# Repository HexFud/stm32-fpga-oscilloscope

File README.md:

# stm32-fpga-oscilloscope
I created a 1-Channel 20MHz 100MS/s Mixed-Signal Digital Storage Oscilloscope on a custom 4-layer PCB. Powered by STM32H7, Lattice iCE40 FPGA, and USB-C from scratch!

## Project overview

The project is made of three parts that were designed together, because each one constrains the others: the PCB decides what the firmware can do, and the heat generated on the PCB decides how the enclosure is built.

| Part | What it covers | Tools |
| :--- | :--- | :--- |
| **PCB** | Schematic and 4-layer layout (see [Schematic and Routing](#schematic-and-routing) and [How this was made](#how-this-was-made)) | KiCad |
| **Firmware** | Acquisition, trigger, signal processing, waveform rendering and UI (see [Firmware](#firmware) and [Firmware architecture](#firmware-architecture)) | STM32CubeIDE, STM32 HAL |
| **CAD** | 3D-printable enclosure (see [Enclosure (CAD)](#enclosure-cad)) | **TODO:** CAD software |

## Schematic and Routing

## How this was made

I have designed the PCB starting from an STM32H7 microcontroller because of its support for external SRAM and it can directly control the main 7 Inch display with high speed transmission data. The entire board runs using a single 5V usb-C connection and then internally this becomes 3.3V, 1.2V and ±5V. The board includes connections for:
- A standard BNC input for oscilloscope probes (1MΩ impedance)
- 2 Rotary encoders and 6 tactile buttons for UI navigation
- A 40-pin FPC socket for an RGB LCD display with a dedicated capacitive touch connector.

## Specifications

| Parameter | Value |
| :--- | :--- |
| Channels | 1 analog |
| Analog bandwidth | 20 MHz |
| Sample rate | 100 MS/s |
| Input | BNC, 1 MΩ, x1 / x10 probes |
| Processing | STM32H7 + Lattice iCE40 FPGA |
| Display | 7" 800x480 RGB LCD, capacitive touch |
| User input | 2 rotary encoders, 6 buttons, touchscreen |
| Power / data | USB-C, 5 V |
| PCB | Custom 4-layer |

## Firmware
The firmware runs on the STM32H7 and is built with STM32CubeIDE and the STM32 HAL. It is responsible for acquisition control, trigger handling, signal processing, rendering the waveform and handling the user interface.

## Display and UI

- Waveform area with a graticule (grid) and a measurement/status bar
- Frame buffer in memory, redrawn on every new acquisition **TODO**
- Controls: one encoder for time base, one for volts/div, buttons for run/stop, single, trigger mode, etc.
- Touchscreen for menus and cursors **TODO**

## Firmware architecture

### Toolchain

| Item | Value |
| :--- | :--- |
| IDE | STM32CubeIDE |
| Drivers | STM32 HAL |
| Language | C |
| Programmer | ST-Link V2 over SWD (J1) |
| Flashing tool | STM32CubeProgrammer |

### Modules

The firmware is organised in layers, from the hardware up to the user interface:

| Layer | Module | Responsibility |
| :--- | :--- | :--- |
| Drivers | Display | Drives the 800x480 RGB panel from a frame buffer |
| Drivers | External memory | Initialises and accesses the external SRAM |
| Drivers | Touch | Reads touch events from the capacitive touch controller |
| Drivers | Input | Reads the 2 encoders and 6 buttons |
| Drivers | FPGA link | Configures the FPGA and transfers captured samples |
| Core | Acquisition | Arms the capture, manages run / stop / single modes and the time base |
| Core | Trigger | Trigger configuration (source, level, slope, mode) |
| Core | Processing | Scaling by volts/div and time/div, measurements |
| UI | Renderer | Draws the graticule, the waveform and the measurement/status bar |
| UI | Controls | Maps encoders, buttons and touch to oscilloscope settings |

### Data flow

1. The ADC samples the input signal and the FPGA captures the samples and evaluates the trigger condition.
2. When a trigger fires, the captured record is transferred to the STM32H7 and stored in memory.
3. The processing stage scales the record to the current volts/div and time/div settings.
4. The renderer draws the graticule and the waveform into the frame buffer, and the display peripheral shows it on screen.
5. Encoder, button and touch events update the settings, and the cycle restarts.

### Testing and debugging

**TODO**

## External connections

1. USB-C Power and Data (P1) this port powers the entire board and it is protected against ESD via a dedicated USBLC6-2SC6 chip
2. Signal Input (J2) It allows you to connect standard x1/x10 oscilloscope probes to measure
3. Programming Port (J1)  Has 3 pins dedicated to flashing and debugging the STM32 microcontroller

| Pin | Function | Where to connect (ST-Link) |
| :---: | :--- | :--- |
| **1** | `SWDIO` | ST-Link SWDIO |
| **2** | `SWCLK` | ST-Link SWCLK |
| **3** | `GND` | ST-Link GND |

## How to flash the firmware

My project uses an STM32H7 chip. To flash the firmware you need an ST-LINK V2 where you need to wire up the correct cable from the usb to the board (J1 connector) and download the free software [STM32CubeProgrammer](https://www.st.com/content/st_com/en/stm32cubeprogrammer.html) and you simply need to upload the firmware.

Steps to reproduce (note that you need to do both):

In STM32CubeIDE:

1. Install STM32CubeIDE
2. Open the project folder inside the IDE
3. Let the IDE resolve the HAL dependencies
4. Go to Project -> Build All to compile the code
5. Wait for the compilation to finish and locate the generated `.bin` or `.elf` file in the `Debug` folder.

In STM32CubeProgrammer:

1. Install the software from the link above
2. Insert the ST-Link V2 USB into the pc
3. Connect the pins explained above (you can power the board via the USB-C port while flashing)
4. In STM32CubeProgrammer ensure that ST-LINK is selected and click connect
5. Go in the erasing & programming tab and select the previously exported `.bin` file
6. Click start programming and if everything went right you'll see Download verified successfully

## Enclosure (CAD)

The enclosure is designed to be 3D printed and to hold the PCB and the 7" display in a single compact unit.

This was designed to:
- Hold the PCB and the 7" display in one unit, with the display window aligned to the active area of the panel
- Expose the BNC input (J2), the USB-C port (P1) and the programming header (J1) without opening the case
- Give access to the 2 rotary encoders and the 6 buttons from the front
- Manage heat: the linear regulators (LDOs) and the FPGA warm up during continuous high-speed sampling, so the enclosure must not trap heat or soften (see the filament recommendation below)

## Filament reccomendation

Because linear regulators (LDOs) and the FPGA generate heat during continuous high-speed sampling, I strongly reccomend to use filaments like PETG, ABS or ASA instead of standard PLA ensuring the plastic won't soften, warp or melt during intensive usage.

## Bill of materials

The full list is in [`bom.csv`](bom.csv). The total is **614.79 USD**. It includes the PCB manufacturing, the 7" display and the parts that are not sourced from LCSC.

## ⚠️⚠️ Safety advice ⚠️⚠️

This project includes experimental software, hardware designs, and assembly documentation are still under development and may contain bugs, errors, or incomplete features. By using, building, or modifying this project, you acknowledge that:

1. You use this project entirely at your own risk
2. You are solely responsible for safe assembly, testing, and operation
3. The autor isn't responsible for any type of damage, injury or loss to people or the machine itself

By proceeding, you accept all risks and agree to these conditions. If you do not acknowledge these risks and conditions, please do not use or build this project.

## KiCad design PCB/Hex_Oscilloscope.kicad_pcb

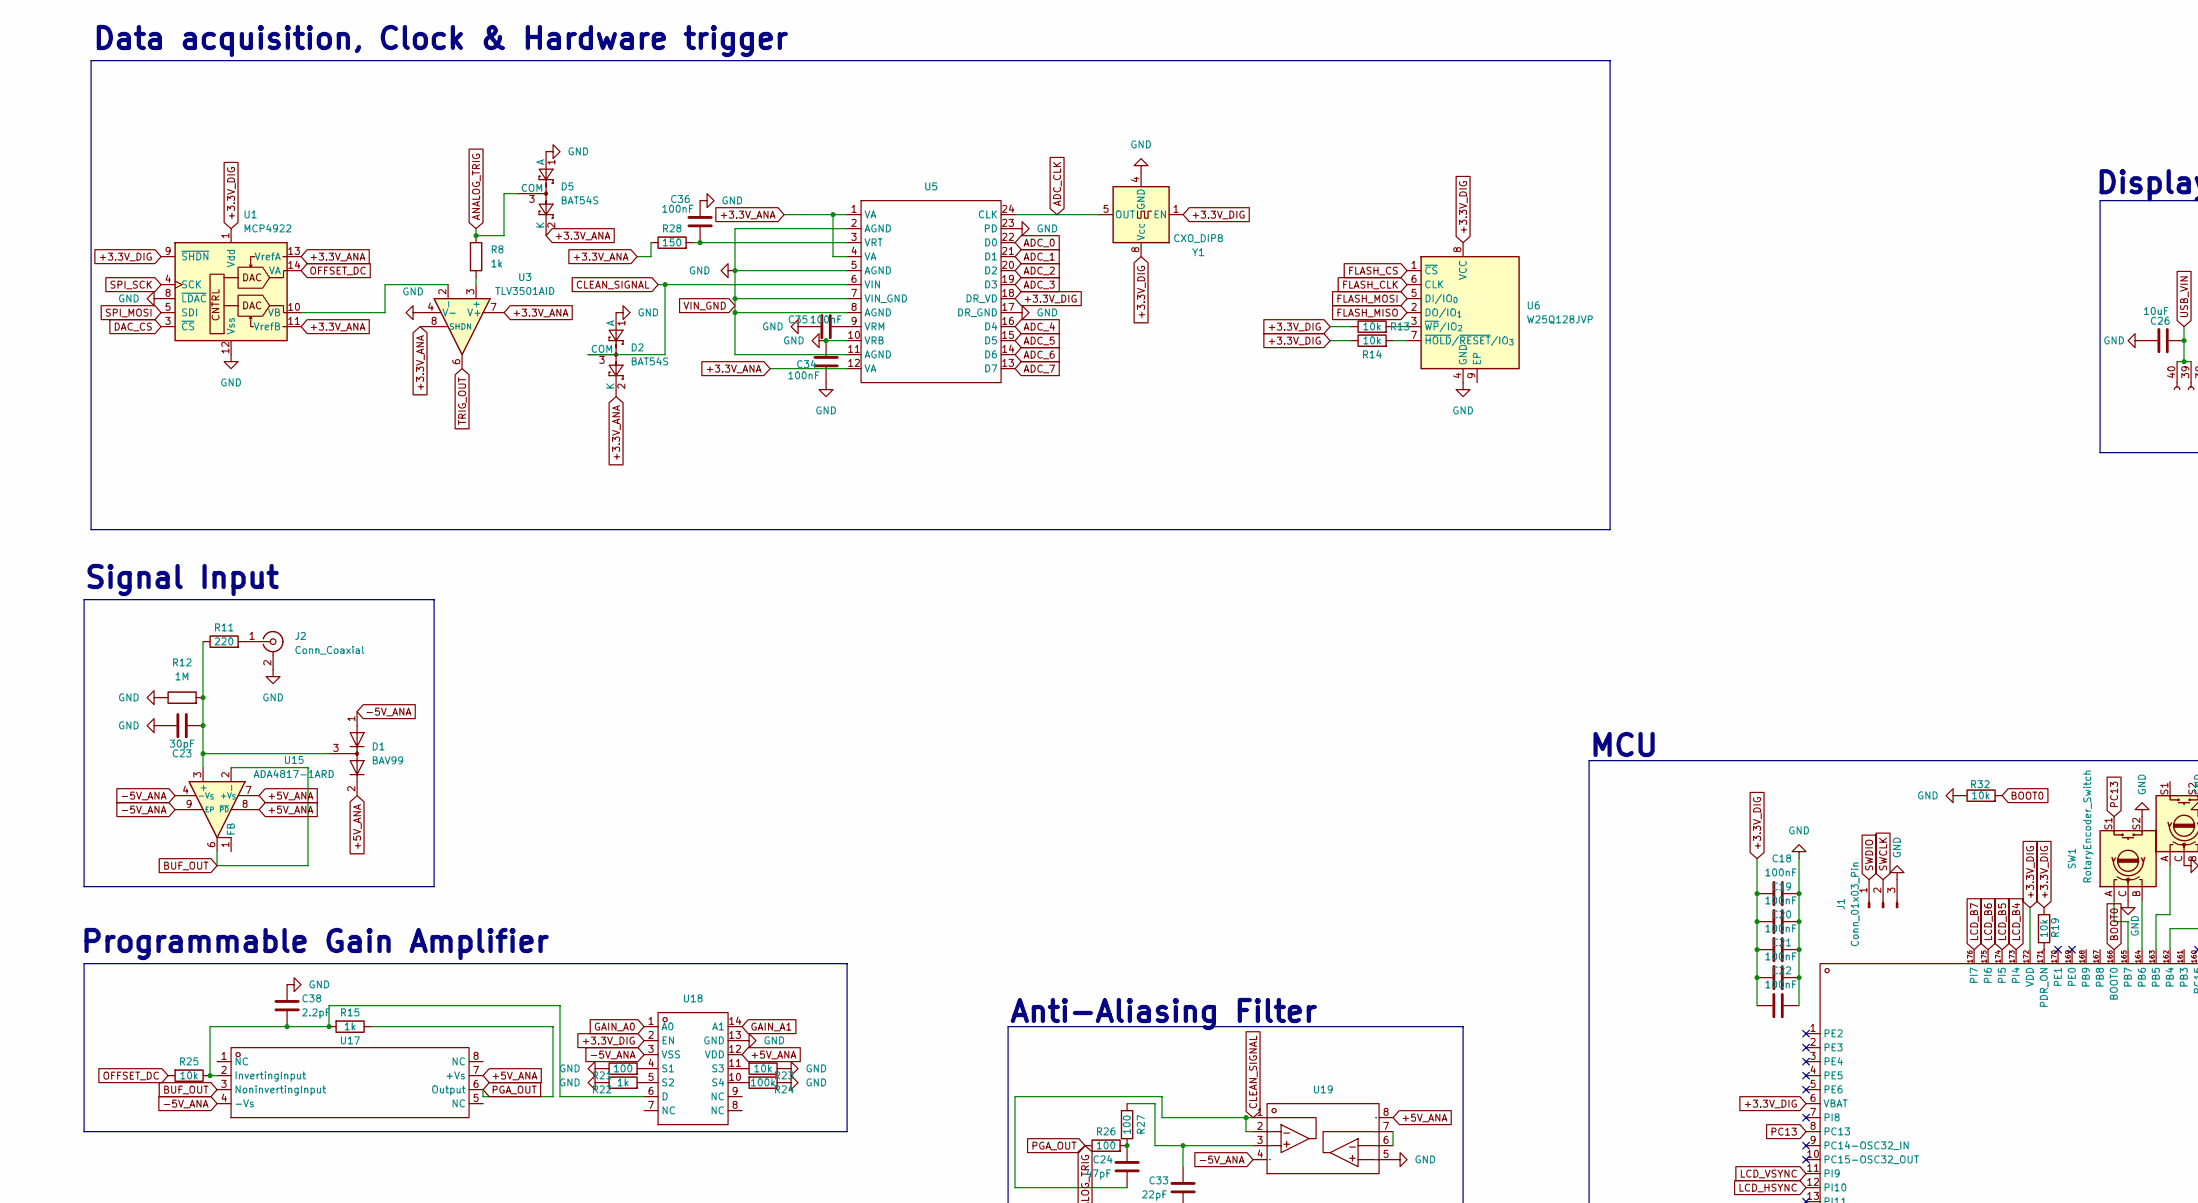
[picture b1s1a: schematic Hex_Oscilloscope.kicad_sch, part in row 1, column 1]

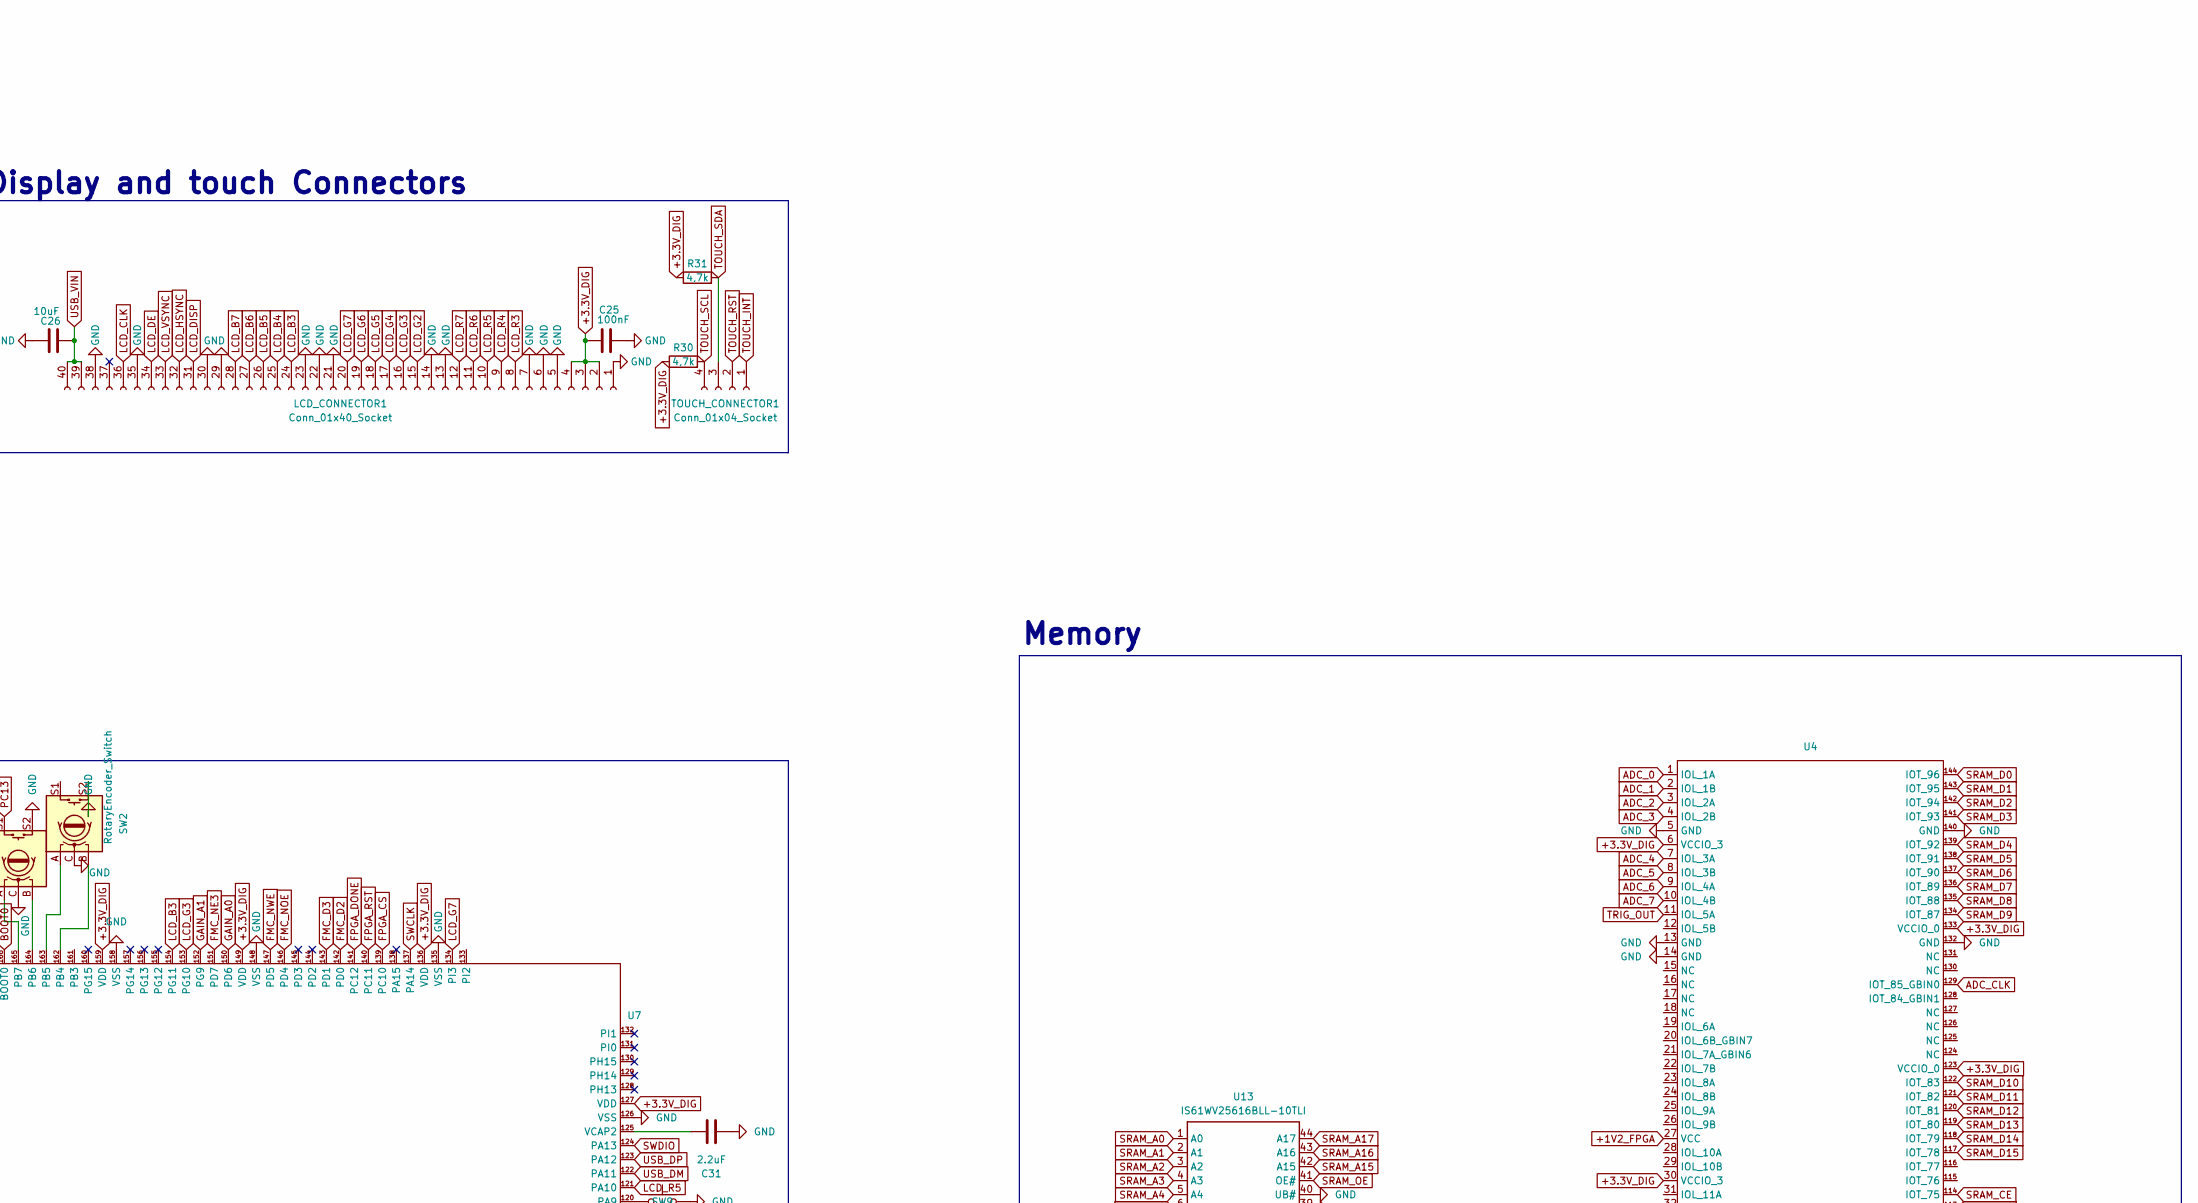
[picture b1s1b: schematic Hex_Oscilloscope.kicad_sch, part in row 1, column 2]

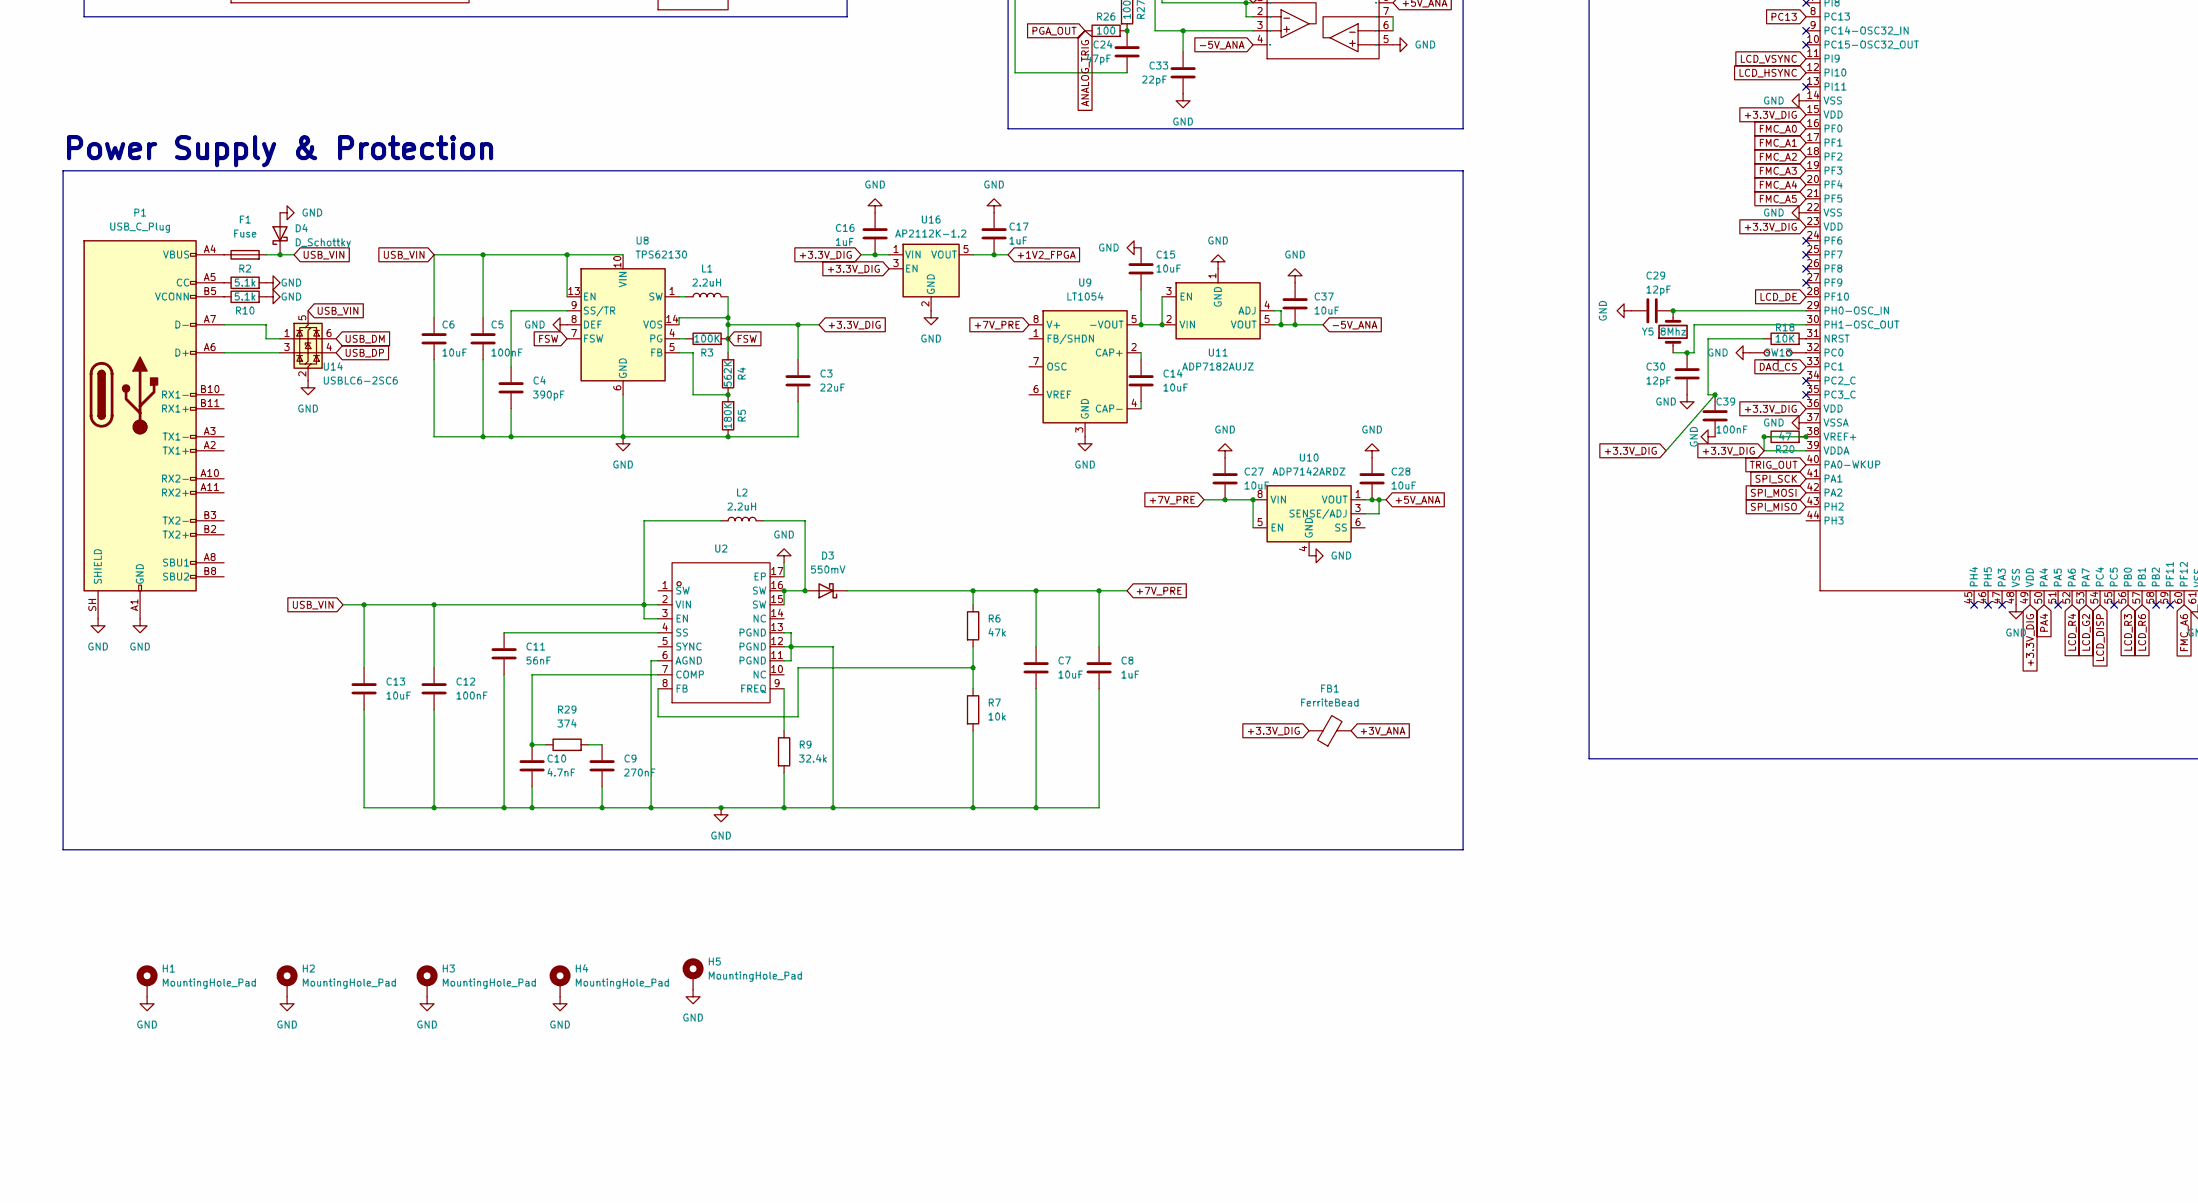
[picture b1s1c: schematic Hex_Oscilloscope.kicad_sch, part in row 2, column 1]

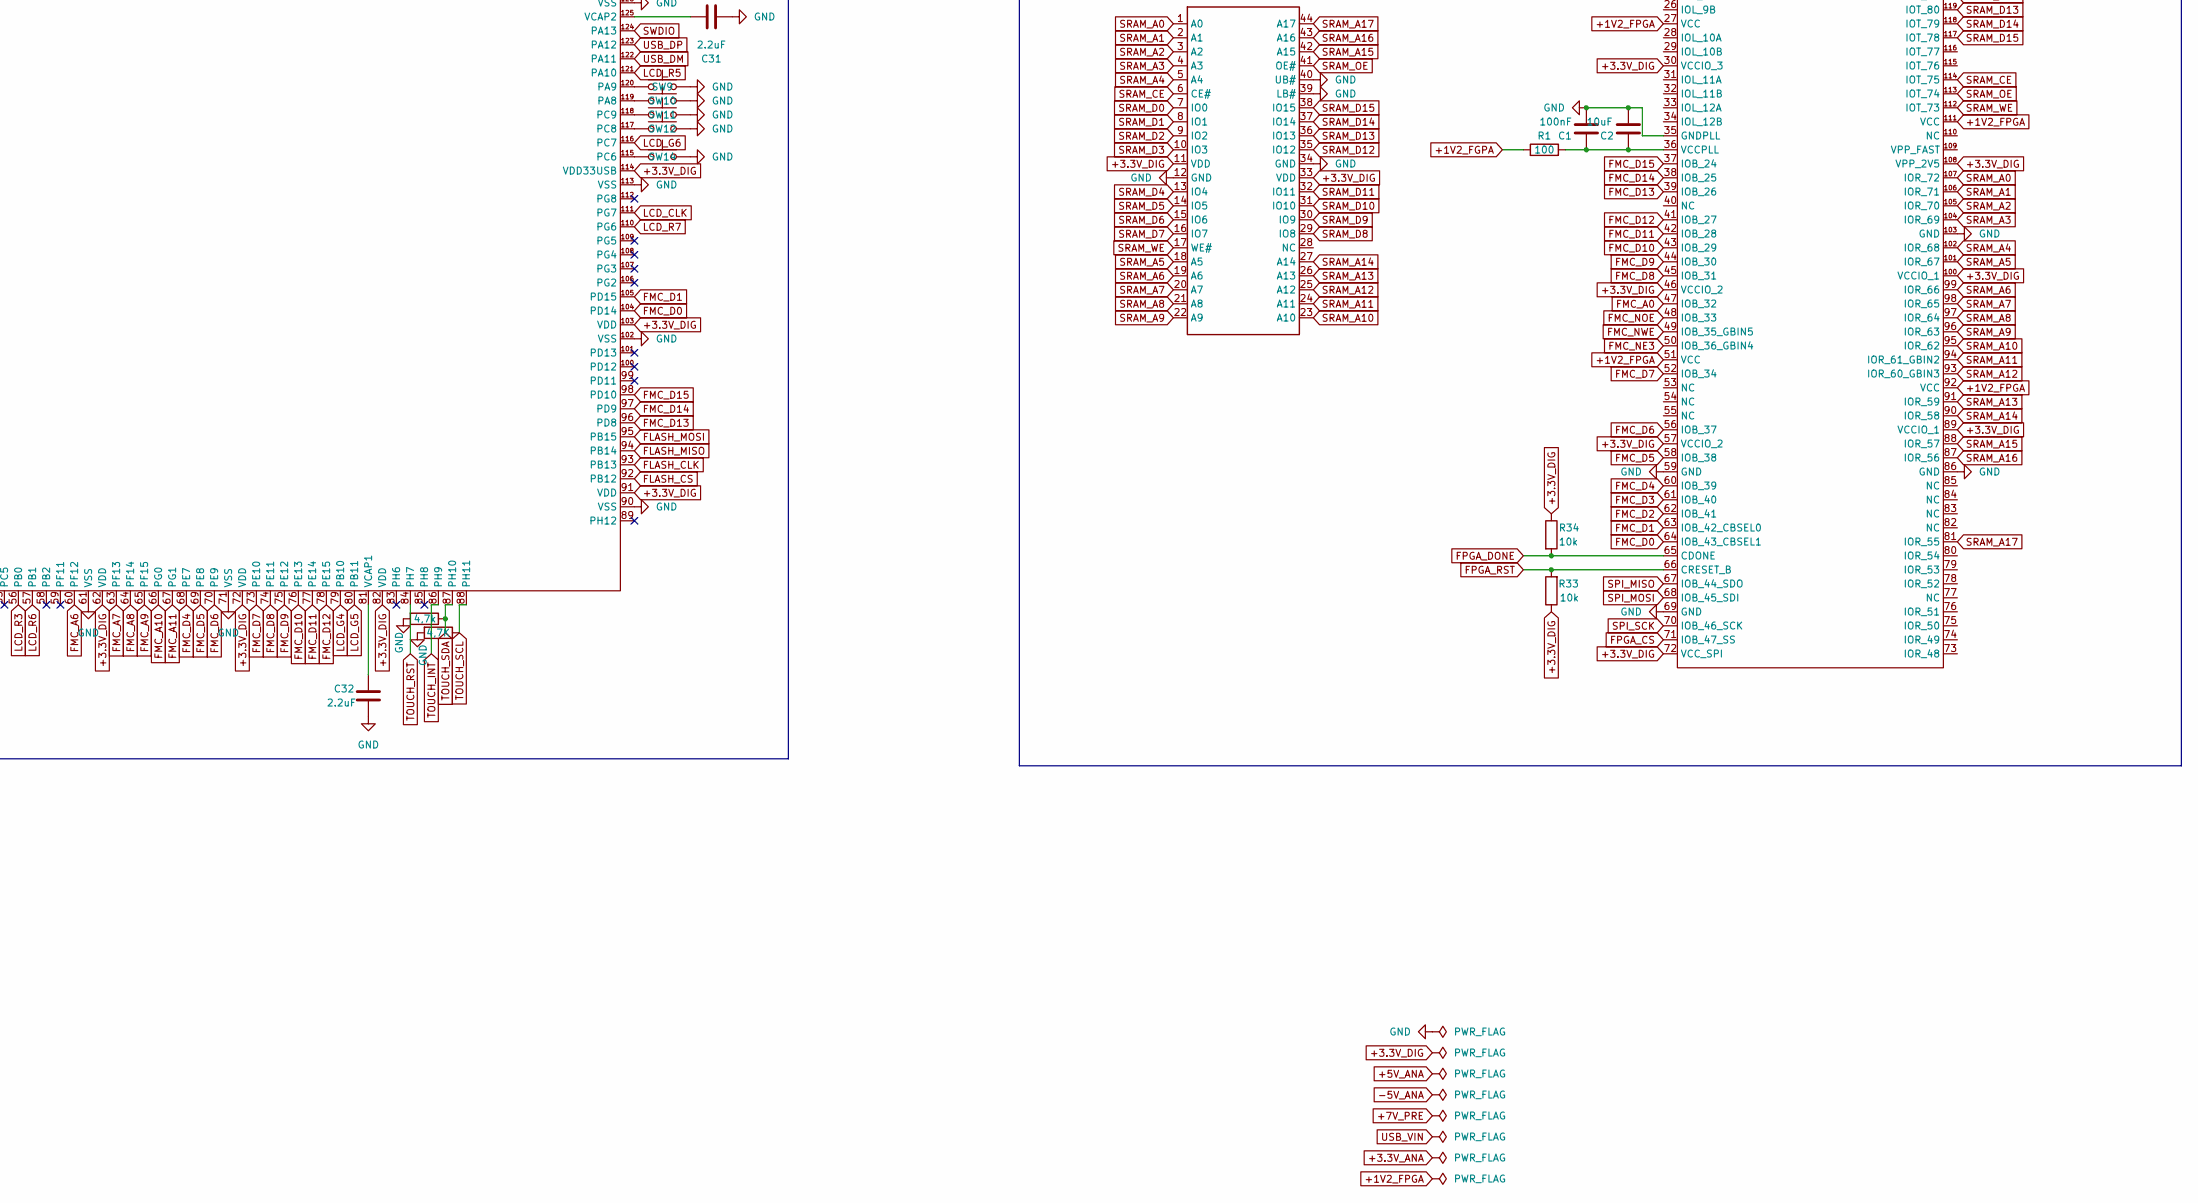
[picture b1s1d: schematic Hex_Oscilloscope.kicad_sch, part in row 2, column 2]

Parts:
C1, C5, C12, C25, C34, C35, C36, C39: 100nF; C_0805_2012Metric
C2, C6, C13, C14, C15, C26, C27, C28, C37: 10uF; C_0805_2012Metric
C3: 22uF; C_0805_2012Metric
C4: 390pF; C_0805_2012Metric
C7: 10uF; C_1210_3225Metric
C8, C16, C17: 1uF; C_0805_2012Metric
C9: 270nF; C_0805_2012Metric
C10: 4.7nF; C_0805_2012Metric
C11: 56nF; C_0805_2012Metric
C18, C19, C20, C21, C22: 100nF; CP_Elec_4x5.4
C23: 30pF; C_0805_2012Metric
C24: 47pF; C_0805_2012Metric
C29, C30: 12pF; C_0805_2012Metric
C31, C32: 2.2uF; C_0805_2012Metric
C33: 22pF; C_0805_2012Metric
C38: 2.2pF; C_0805_2012Metric
D1: BAV99; SOT-23
D2, D5: BAT54S; SOT-23
D3: 550mV; D_SMA
D4: D_Schottky; D_SMB
F1: Fuse; Fuse_1206_3216Metric
FB1: FerriteBead; L_0805_2012Metric
H1, H2, H3, H4, H5: MountingHole_Pad; MountingHole_3.2mm_M3_Pad
J1: Conn_01x03_Pin; PinHeader_1x03_P2.54mm_Vertical
J2: Conn_Coaxial; BNC_Amphenol_031-6575_Horizontal
L1: 2.2uH; L_6.3x6.3_H3
L2: 2.2uH; L_10.4x10.4_H4.8
LCD_CONNECTOR1: Conn_01x40_Socket; Hirose_FH12-40S-0.5SH_1x40-1MP_P0.50mm_Horizontal
P1: USB_C_Plug; USB_C_Receptacle_GCT_USB4110
R1, R21, R26, R27: 100; R_0805_2012Metric
R2, R10: 5.1k; R_0805_2012Metric
R3: 100K; R_0805_2012Metric
R4: 562K; R_0805_2012Metric
R5: 180K; R_0805_2012Metric
R6: 47k; R_0805_2012Metric
R7, R13, R14, R19, R23, R25, R32, R33, R34: 10k; R_0805_2012Metric
R8, R15, R22: 1k; R_0805_2012Metric
R9: 32.4k; R_0805_2012Metric
R11: 220; R_0805_2012Metric
R12: 1M; R_0805_2012Metric
R16, R30, R31: 4,7k; R_0805_2012Metric
R17: 4,7K; R_0805_2012Metric
R18: 10K; R_0805_2012Metric
R20: 47; R_0805_2012Metric
R24: 100k; R_0805_2012Metric
R28: 150; R_0805_2012Metric
R29: 374; R_0805_2012Metric
SW1, SW2: RotaryEncoder_Switch; RotaryEncoder_Alps_EC11E-Switch_Vertical_H20mm
SW9, SW10, SW11, SW12, SW13, SW14: SW_Push; SW_SPST_B3U-1000P
TOUCH_CONNECTOR1: Conn_01x04_Socket; Molex_200528-0040_1x04-1MP_P1.00mm_Horizontal
U1: MCP4922; TSSOP-14_4.4x5mm_P0.65mm
U2: QFN-16_L3.0-W3.0-P0.50-BL-EP1.7; Manufacturer Part TPS55340QRTETQ1; LCSC Part Name 升压型 5.25A 2.9V~38V
U3: TLV3501AID; SOIC-8_3.9x4.9mm_P1.27mm
U4: TQFP-144_L20.0-W20.0-P0.50-LS22.0-BL; Manufacturer Part ICE40HX4K-TQ144; LCSC Part Name 超低功耗、非易失FPGA
U5: TSSOP-24_L7.8-W4.4-P0.65-LS6.4-BL; Manufacturer Part ADC08100CIMTC; LCSC Part Name 8 位 100MSPS 1.3mW/MSPS 模数转换器(ADC)
U6: W25Q128JVP; WSON-8-1EP_6x5mm_P1.27mm_EP3.4x4.3mm
U7: LQFP-176_L24.0-W24.0-P0.50-LS26.0-BL; Manufacturer Part STM32H743IIT6; LCSC Part Name 带DSP和DP-FPU的高性能ARM Cortex-M7 MCU，具有2 MB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
U8: TPS62130; VQFN-16-1EP_3x3mm_P0.5mm_EP1.68x1.68mm_ThermalVias
U9: LT1054; SOIC-8_3.9x4.9mm_P1.27mm
U10: ADP7142ARDZ; SOIC-8-1EP_3.9x4.9mm_P1.27mm_EP2.29x3mm
U11: ADP7182AUJZ; TSOT-23-5
U13: IS61WV25616BLL-10TLI; TSOP-44_L18.4-W10.2-P0.80-LS11.8-BL; Manufacturer Part IS61WV25616BLL-10TLI; LCSC Part Name 256KX16高速异步CMOS静态RAM
U14: USBLC6-2SC6; SOT-23-6
U15: ADA4817-1ARD; SOIC-8-1EP_3.9x4.9mm_P1.27mm_EP2.29x3mm
U16: AP2112K-1.2; SOT-23-5
U17: SOP-8_L4.9-W3.9-P1.27-LS6.0-TL; Manufacturer Part OPA820IDR; LCSC Part Name OPA820IDR
U18: TSSOP-14_L5.0-W4.4-P0.65-LS6.4-BL; Manufacturer Part ADG1204YRUZ; LCSC Part Name 低电容、低电荷注入±15 V/+12 V, 4:1 iCMOS多路复用器
U19: SOP-8_L4.9-W3.9-P1.27-LS6.0-BL; Manufacturer Part AD8058ARZ; LCSC Part Name 低成本、高性能电压反馈型325 MHz放大器
Y1: CXO_DIP8; Oscillator_DIP-8
Y5: 8Mhz; Crystal_SMD_3225-4Pin_3.2x2.5mm

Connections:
+1V2_FGPA: R1.1
+1V2_FPGA: C17.2, U4.27 (VCC), U4.51 (VCC), U4.92 (VCC), U4.111 (VCC), U16.5 (VOUT)
+3.3V_ANA: D2.2 (K), D5.2 (K), R28.1, U1.11 (VrefB), U1.13 (VrefA), U3.7 (V+), U3.8 (SHDN), U5.1 (VA), U5.4 (VA), U5.12 (VA)
+3.3V_DIG: C3.1, C16.2, C18.1, C19.1, C20.1, C21.1, C22.1, C25.1, C39.1, FB1.1, L1.2, LCD_CONNECTOR1.2, LCD_CONNECTOR1.3, LCD_CONNECTOR1.4, R3.2, R4.2, R13.1, R14.1, R18.1, R19.1, R20.1, R20.2, R30.1, R31.1, R33.1, R34.1, U1.1 (Vdd), U1.9 (~SHDN), U4.6 (VCCIO_3), U4.30 (VCCIO_3), U4.46 (VCCIO_2), U4.57 (VCCIO_2), U4.72 (VCC_SPI), U4.89 (VCCIO_1), U4.100 (VCCIO_1), U4.108 (VPP_2V5), U4.123 (VCCIO_0), U4.133 (VCCIO_0), U5.18 (DR_VD), U6.8 (VCC), U7.6 (VBAT), U7.15 (VDD), U7.23 (VDD), U7.36 (VDD), U7.38 (VREF+), U7.39 (VDDA), U7.49 (VDD), U7.62 (VDD), U7.72 (VDD), U7.82 (VDD), U7.91 (VDD), U7.103 (VDD), U7.114 (VDD33USB), U7.127 (VDD), U7.136 (VDD), U7.149 (VDD), U7.159 (VDD), U7.172 (VDD), U8.7 (FSW), U8.14 (VOS), U13.11 (VDD), U13.33 (VDD), U16.1 (VIN), U16.3 (EN), U18.2 (EN), Y1.1 (EN), Y1.8 (Vcc)
+3V_ANA: FB1.2
+5V_ANA: C28.2, D1.2 (A), U10.1 (VOUT), U10.2 (VOUT), U10.3 (SENSE/ADJ), U15.7 (+V_{S}), U15.8 (~PD), U17.7 (+Vs), U18.12 (VDD), U19.8 (VS+)
+7V_PRE: C7.1, C8.1, C27.2, D3.1 (K), R6.1, U9.8 (V+), U10.5 (EN), U10.7 (VIN), U10.8 (VIN)
-5V_ANA: C37.2, D1.1 (K), U11.4 (ADJ), U11.5 (VOUT), U15.4 (-V_{S}), U15.9 (EP), U17.4 (-Vs), U18.3 (VSS), U19.4 (VS-)
ADC_0: U4.1 (IOL_1A), U5.22 (D0)
ADC_1: U4.2 (IOL_1B), U5.21 (D1)
ADC_2: U4.3 (IOL_2A), U5.20 (D2)
ADC_3: U4.4 (IOL_2B), U5.19 (D3)
ADC_4: U4.7 (IOL_3A), U5.16 (D4)
ADC_5: U4.8 (IOL_3B), U5.15 (D5)
ADC_6: U4.9 (IOL_4A), U5.14 (D6)
ADC_7: U4.10 (IOL_4B), U5.13 (D7)
ADC_CLK: U4.129 (IOT_85_GBIN0), U5.24 (CLK), Y1.5 (OUT)
ANALOG_TRIG: D5.3 (COM), R8.1, R15.1, R26.1, U17.6 (Output)
BOOT0: R32.2, U7.166 (BOOT0)
BUF_OUT: U15.2 (-), U15.6, U17.3 (NoninvertingInput)
CLEAN_SIGNAL: C24.2, D2.3 (COM), U5.6 (VIN), U19.1 (OUT1), U19.2 (IN1-)
DAC_CS: U1.3 (~CS), U7.33 (PC1)
FLASH_CLK: U6.6 (CLK), U7.93 (PB13)
FLASH_CS: U6.1 (~CS), U7.92 (PB12)
FLASH_MISO: U6.2 (DO/IO_{1}), U7.94 (PB14)
FLASH_MOSI: U6.5 (DI/IO_{0}), U7.95 (PB15)
FMC_A0: U4.47 (IOB_32), U7.16 (PF0)
FMC_A1: U7.17 (PF1)
FMC_A2: U7.18 (PF2)
FMC_A3: U7.19 (PF3)
FMC_A4: U7.20 (PF4)
FMC_A5: U7.21 (PF5)
FMC_A6: U7.60 (PF12)
FMC_A7: U7.63 (PF13)
FMC_A8: U7.64 (PF14)
FMC_A9: U7.65 (PF15)
FMC_A10: U7.66 (PG0)
FMC_A11: U7.67 (PG1)
FMC_D0: U4.64 (IOB_43_CBSEL1), U7.104 (PD14)
FMC_D1: U4.63 (IOB_42_CBSEL0), U7.105 (PD15)
FMC_D2: U4.62 (IOB_41), U7.142 (PD0)
FMC_D3: U4.61 (IOB_40), U7.143 (PD1)
FMC_D4: U4.60 (IOB_39), U7.68 (PE7)
FMC_D5: U4.58 (IOB_38), U7.69 (PE8)
FMC_D6: U4.56 (IOB_37), U7.70 (PE9)
FMC_D7: U4.52 (IOB_34), U7.73 (PE10)
FMC_D8: U4.45 (IOB_31), U7.74 (PE11)
FMC_D9: U4.44 (IOB_30), U7.75 (PE12)
FMC_D10: U4.43 (IOB_29), U7.76 (PE13)
FMC_D11: U4.42 (IOB_28), U7.77 (PE14)
FMC_D12: U4.41 (IOB_27), U7.78 (PE15)
FMC_D13: U4.39 (IOB_26), U7.96 (PD8)
FMC_D14: U4.38 (IOB_25), U7.97 (PD9)
FMC_D15: U4.37 (IOB_24), U7.98 (PD10)
FMC_NE3: U4.50 (IOB_36_GBIN4), U7.151 (PD7)
FMC_NOE: U4.48 (IOB_33), U7.146 (PD4)
FMC_NWE: U4.49 (IOB_35_GBIN5), U7.147 (PD5)
FPGA_CS: U4.71 (IOB_47_SS), U7.139 (PC10)
FPGA_DONE: R34.2, U4.65 (CDONE), U7.141 (PC12)
FPGA_RST: R33.2, U4.66 (CRESET_B), U7.140 (PC11)
GAIN_A0: U7.150 (PD6), U18.1 (A0)
GAIN_A1: U7.152 (PG9), U18.14 (A1)
LCD_B3: LCD_CONNECTOR1.24, U7.154 (PG11)
LCD_B4: LCD_CONNECTOR1.25, U7.173 (PI4)
LCD_B5: LCD_CONNECTOR1.26, U7.174 (PI5)
LCD_B6: LCD_CONNECTOR1.27, U7.175 (PI6)
LCD_B7: LCD_CONNECTOR1.28, U7.176 (PI7)
LCD_CLK: LCD_CONNECTOR1.36, U7.111 (PG7)
LCD_DE: LCD_CONNECTOR1.34, U7.28 (PF10)
LCD_DISP: LCD_CONNECTOR1.31, U7.54 (PC4)
LCD_G2: LCD_CONNECTOR1.15, U7.53 (PA7)
LCD_G3: LCD_CONNECTOR1.16, U7.153 (PG10)
LCD_G4: LCD_CONNECTOR1.17, U7.79 (PB10)
LCD_G5: LCD_CONNECTOR1.18, U7.80 (PB11)
LCD_G6: LCD_CONNECTOR1.19, U7.116 (PC7)
LCD_G7: LCD_CONNECTOR1.20, U7.134 (PI3)
LCD_HSYNC: LCD_CONNECTOR1.32, U7.12 (PI10)
LCD_R3: LCD_CONNECTOR1.8, U7.56 (PB0)
LCD_R4: LCD_CONNECTOR1.9, U7.52 (PA6)
LCD_R5: LCD_CONNECTOR1.10, U7.121 (PA10)
LCD_R6: LCD_CONNECTOR1.11, U7.57 (PB1)
LCD_R7: LCD_CONNECTOR1.12, U7.110 (PG6)
LCD_VSYNC: LCD_CONNECTOR1.33, U7.11 (PI9)
unnamed: C9.1, R29.2
unnamed: C24.1, R26.2, R27.2
unnamed: D3.2 (A), L2.2, U2.15 (SW), U2.16 (SW)
unnamed: F1.1, P1.A4 (VBUS), P1.A9 (VBUS), P1.B4 (VBUS), P1.B9 (VBUS)
unnamed: J2.1 (In), R11.2
unnamed: L1.1, U8.1 (SW), U8.2 (SW), U8.3 (SW)
unnamed: P1.A5 (CC), R2.1
unnamed: P1.A6 (D+), U14.3 (I/O2)
unnamed: P1.A7 (D-), U14.1 (I/O1)
unnamed: P1.B5 (VCONN), R10.1
unnamed: U1.10 (VB), U3.2 (-)
unnamed: C10.1, R29.1, U2.7 (COMP)
unnamed: R6.2, R7.1, U2.8 (FB)
unnamed: R9.1, U2.9 (FREQ)
unnamed: C11.1, U2.4 (SS)
unnamed: R8.2, U3.3 (+)
unnamed: C1.1, C2.1, R1.2, U4.36 (VCCPLL)
unnamed: C35.2, U5.9 (VRM)
unnamed: C36.2, R28.2, U5.3 (VRT)
unnamed: R14.2, U6.7 (~HOLD/~RESET/IO_{3})
unnamed: R13.2, U6.3 (~WP/IO_{2})
unnamed: R18.2, U7.31 (NRST)
unnamed: SW10.1, U7.119 (PA8)
unnamed: SW9.1, U7.120 (PA9)
unnamed: SW2.B, U7.162 (PB4)
unnamed: SW2.A, U7.163 (PB5)
unnamed: SW1.B, U7.164 (PB6)
unnamed: SW1.A, U7.165 (PB7)
unnamed: SW13.1, U7.32 (PC0)
unnamed: SW14.1, U7.115 (PC6)
unnamed: SW12.1, U7.117 (PC8)
unnamed: SW11.1, U7.118 (PC9)
unnamed: R19.2, U7.171 (PDR_ON)
unnamed: C29.2, U7.29 (PH0-OSC_IN), Y5.2
unnamed: C30.1, U7.30 (PH1-OSC_OUT), Y5.1
unnamed: C32.2, U7.81 (VCAP1)
unnamed: C31.2, U7.125 (VCAP2)
unnamed: R4.1, R5.2, U8.5 (FB)
unnamed: R3.1, U8.4 (PG)
unnamed: C4.1, U8.9 (SS/TR)
unnamed: C14.1, U9.2 (CAP+)
unnamed: C14.2, U9.4 (CAP-)
unnamed: C15.1, U9.5 (-VOUT), U11.2 (VIN), U11.3 (EN)
unnamed: C23.2, D1.3 (K), R11.1, R12.2, U15.3 (+)
unnamed: C38.2, R15.2, R25.1, U17.2 (InvertingInput), U18.6 (D)
unnamed: R21.2, U18.4 (S1)
unnamed: R22.2, U18.5 (S2)
unnamed: R23.2, U18.11 (S3)
unnamed: R24.2, U18.10 (S4)
unnamed: C33.1, R27.1, U19.3 (IN1+)
unnamed: U19.6 (IN2-), U19.7 (OUT2)
OFFSET_DC: R25.2, U1.14 (VA)
PA4: U7.50 (PA4)
PC13: SW1.S1, U7.8 (PC13)
SPI_MISO: U4.67 (IOB_44_SDO), U7.43 (PH2)
SPI_MOSI: U1.5 (SDI), U4.68 (IOB_45_SDI), U7.42 (PA2)
SPI_SCK: U1.4 (SCK), U4.70 (IOB_46_SCK), U7.41 (PA1)
SRAM_A0: U4.107 (IOR_72), U13.1 (A0)
SRAM_A1: U4.106 (IOR_71), U13.2 (A1)
SRAM_A2: U4.105 (IOR_70), U13.3 (A2)
SRAM_A3: U4.104 (IOR_69), U13.4 (A3)
SRAM_A4: U4.102 (IOR_68), U13.5 (A4)
SRAM_A5: U4.101 (IOR_67), U13.18 (A5)
SRAM_A6: U4.99 (IOR_66), U13.19 (A6)
SRAM_A7: U4.98 (IOR_65), U13.20 (A7)
SRAM_A8: U4.97 (IOR_64), U13.21 (A8)
SRAM_A9: U4.96 (IOR_63), U13.22 (A9)
SRAM_A10: U4.95 (IOR_62), U13.23 (A10)
SRAM_A11: U4.94 (IOR_61_GBIN2), U13.24 (A11)
SRAM_A12: U4.93 (IOR_60_GBIN3), U13.25 (A12)
SRAM_A13: U4.91 (IOR_59), U13.26 (A13)
SRAM_A14: U4.90 (IOR_58), U13.27 (A14)
SRAM_A15: U4.88 (IOR_57), U13.42 (A15)
SRAM_A16: U4.87 (IOR_56), U13.43 (A16)
SRAM_A17: U4.81 (IOR_55), U13.44 (A17)
SRAM_CE: U4.114 (IOT_75), U13.6 (CE#)
SRAM_D0: U4.144 (IOT_96), U13.7 (IO0)
SRAM_D1: U4.143 (IOT_95), U13.8 (IO1)
SRAM_D2: U4.142 (IOT_94), U13.9 (IO2)
SRAM_D3: U4.141 (IOT_93), U13.10 (IO3)
SRAM_D4: U4.139 (IOT_92), U13.13 (IO4)
SRAM_D5: U4.138 (IOT_91), U13.14 (IO5)
SRAM_D6: U4.137 (IOT_90), U13.15 (IO6)
SRAM_D7: U4.136 (IOT_89), U13.16 (IO7)
SRAM_D8: U4.135 (IOT_88), U13.29 (IO8)
SRAM_D9: U4.134 (IOT_87), U13.30 (IO9)
SRAM_D10: U4.122 (IOT_83), U13.31 (IO10)
SRAM_D11: U4.121 (IOT_82), U13.32 (IO11)
SRAM_D12: U4.120 (IOT_81), U13.35 (IO12)
SRAM_D13: U4.119 (IOT_80), U13.36 (IO13)
SRAM_D14: U4.118 (IOT_79), U13.37 (IO14)
SRAM_D15: U4.117 (IOT_78), U13.38 (IO15)
SRAM_OE: U4.113 (IOT_74), U13.41 (OE#)
SRAM_WE: U4.112 (IOT_73), U13.17 (WE#)
SWCLK: J1.2, U7.137 (PA14)
SWDIO: J1.1, U7.124 (PA13)
TOUCH_INT: TOUCH_CONNECTOR1.1, U7.86 (PH9)
TOUCH_RST: TOUCH_CONNECTOR1.2, U7.84 (PH7)
TOUCH_SCL: R17.1, R30.2, TOUCH_CONNECTOR1.4, U7.88 (PH11)
TOUCH_SDA: R16.1, R31.2, TOUCH_CONNECTOR1.3, U7.87 (PH10)
TRIG_OUT: U3.6, U4.11 (IOL_5A), U7.40 (PA0-WKUP)
USB_DM: U7.122 (PA11), U14.6 (I/O1)
USB_DP: U7.123 (PA12), U14.4 (I/O2)
USB_VIN: C5.1, C6.1, C12.1, C13.1, C26.1, D4.1 (K), F1.2, L2.1, LCD_CONNECTOR1.39, LCD_CONNECTOR1.40, U2.2 (VIN), U2.3 (EN), U8.10 (VIN), U8.11 (VIN), U8.12 (VIN), U8.13 (EN), U14.5 (VBUS)
VIN_GND: C1.2, C2.2, C3.2, C4.2, C5.2, C6.2, C7.2, C8.2, C9.2, C10.2, C11.2, C12.2, C13.2, C15.2, C16.1, C17.1, C18.2, C19.2, C20.2, C21.2, C22.2, C23.1, C25.2, C26.2, C27.1, C28.1, C29.1, C30.2, C31.1, C32.1, C33.2, C34.1, C34.2, C35.1, C36.1, C37.1, C38.1, C39.2, D2.1 (A), D4.2 (A), D5.1 (A), H1.1 (1_1), H2.1 (1_1), H3.1 (1_1), H4.1 (1_1), H5.1 (1_1), J1.3, J2.2 (Ext), LCD_CONNECTOR1.1, LCD_CONNECTOR1.5, LCD_CONNECTOR1.6, LCD_CONNECTOR1.7, LCD_CONNECTOR1.13, LCD_CONNECTOR1.14, LCD_CONNECTOR1.21, LCD_CONNECTOR1.22, LCD_CONNECTOR1.23, LCD_CONNECTOR1.29, LCD_CONNECTOR1.30, LCD_CONNECTOR1.35, LCD_CONNECTOR1.38, P1.A1 (GND), P1.A12 (GND), P1.B1 (GND), P1.B12 (GND), P1.SH (SHIELD), R2.2, R5.1, R7.2, R9.2, R10.2, R12.1, R16.2, R17.2, R21.1, R22.1, R23.1, R24.1, R32.1, SW1.C, SW1.S2, SW2.C, SW2.S2, SW9.2, SW10.2, SW11.2, SW12.2, SW13.2, SW14.2, U1.8 (~LDAC), U1.12 (Vss), U2.6 (AGND), U2.11 (PGND), U2.12 (PGND), U2.13 (PGND), U2.17 (EP), U3.4 (V-), U4.5 (GND), U4.13 (GND), U4.14 (GND), U4.35 (GNDPLL), U4.59 (GND), U4.69 (GND), U4.86 (GND), U4.103 (GND), U4.132 (GND), U4.140 (GND), U5.2 (AGND), U5.5 (AGND), U5.7 (VIN_GND), U5.8 (AGND), U5.10 (VRB), U5.11 (AGND), U5.17 (DR_GND), U5.23 (PD), U6.4 (GND), U7.14 (VSS), U7.22 (VSS), U7.37 (VSSA), U7.48 (VSS), U7.61 (VSS), U7.71 (VSS), U7.90 (VSS), U7.102 (VSS), U7.113 (VSS), U7.126 (VSS), U7.135 (VSS), U7.148 (VSS), U7.158 (VSS), U8.6 (GND), U8.8 (DEF), U8.15 (GND), U8.16 (GND), U8.17 (GND), U9.3 (GND), U10.4 (GND), U10.9 (GND), U11.1 (GND), U13.12 (GND), U13.34 (GND), U13.39 (LB#), U13.40 (UB#), U14.2 (GND), U16.2 (GND), U18.13 (GND), U19.5 (IN2+), Y1.4 (GND)

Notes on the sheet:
Data acquisition, Clock & Hardware trigger
Anti-Aliasing Filter
Signal Input
MCU
Programmable Gain Amplifier
Memory
Display and touch Connectors
Power Supply & Protection

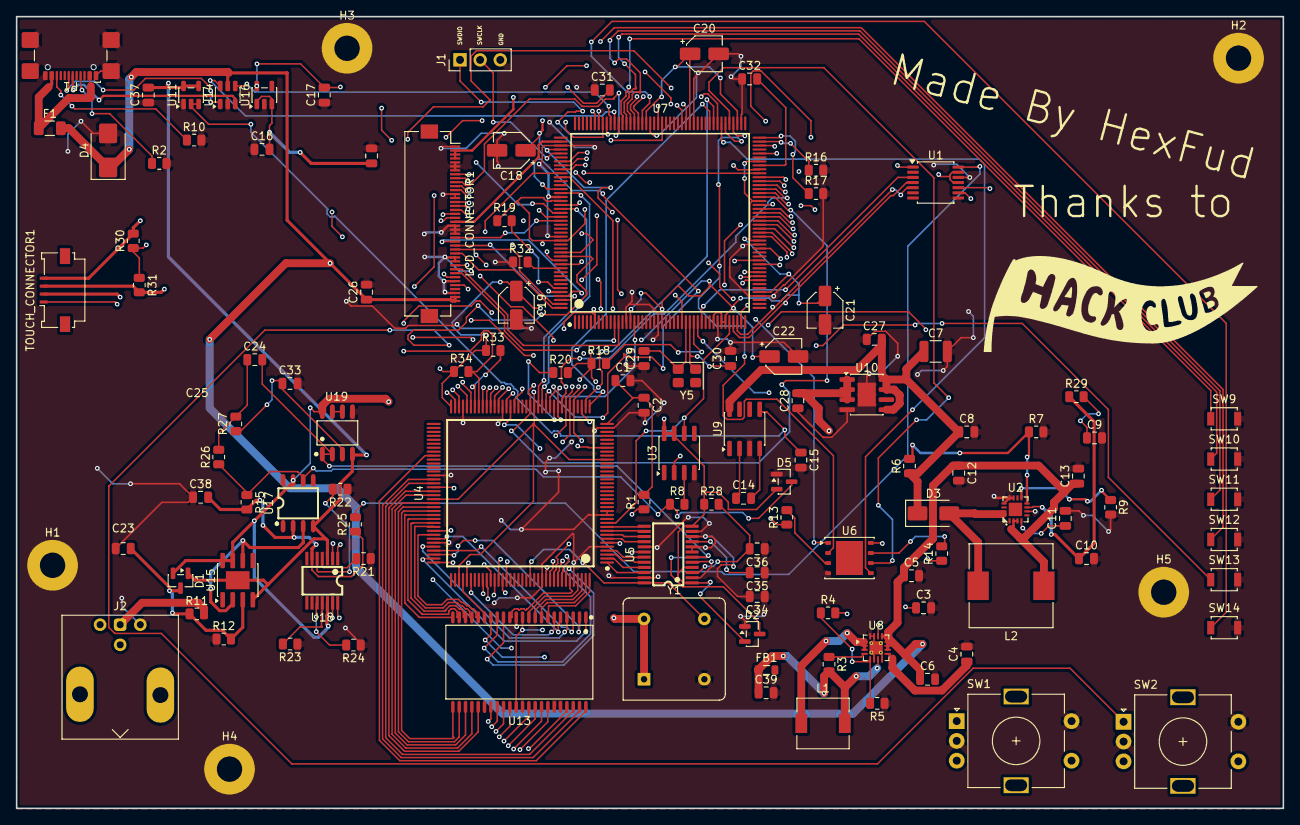
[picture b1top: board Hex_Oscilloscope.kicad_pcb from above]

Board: 4 copper layers, 160.0 x 100.0 mm, 120 parts (0 on the bottom side), 174 nets.
